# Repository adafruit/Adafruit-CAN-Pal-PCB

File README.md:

## Adafruit CAN Pal - CAN Bus Transciever - TJA1051T/3 PCB

<a href="http://www.adafruit.com/products/5708"><br/>
Click here to purchase one from the Adafruit shop</a>

PCB files for the Adafruit CAN Pal - CAN Bus Transciever - TJA1051T/3. 

Format is EagleCAD schematic and board layout
* https://www.adafruit.com/product/5708

### Description

If you'd like to connect a board with native CAN Peripheral support, the Adafruit CAN Pal Transceiver will take the 3V logic level signals and convert them to CAN logic levels with the differential signaling required to communicate. Note that not all chips have a CAN peripheral! Some that we know do have it are the ESP32/ESP32-S2/ESP32-S3 (note that ESP32 calls this interface TWAI not CAN) series of chips, SAME51, STM32F405, or Teensy 4.

Check the product documentation for the board you are wiring this to, to make sure that the chip has CAN support and the RX and TX pins are brought out for you to connect the transceiver to! Despite sharing the 'RX' and 'TX' name with UART, they're not at all the same interface.

CAN Bus is a small-scale networking standard, originally designed for cars and, yes, busses, but is now used for many robotics or sensor networks that need better range and addressing than I2C, and don't have the pins or computational ability to talk on Ethernet. CAN is 2 wire differential, which means it's good for long distances and noisy environments.

Messages are sent at about 1Mbps rate - you set the frequency for the bus and then all 'joiners' must match it, and have an address before the packet so that each node can listen in to messages just for it. New nodes can be attached easily because they just need to connect to the two data lines anywhere in the shared net. Each CAN devices sends messages whenever it wants, and thanks to some clever data encoding, can detect if there's a message collision and retransmit later. 

We've added a few nice extras to this breakout pal to make it useful in many common CAN scenarios:

* TJA1051/T3 can communicate with 3.3V~5V logic for use with modern microcontrollers. 
* 5V charge-pump voltage generator, so even though you are running 3.3V power and logic on most modern microcontroller boards, it will generate a nice clean 5V as required by the transceiver. No separate 5V power required!
* 3.5mm terminal block that can be soldered in to get quick access to the High and Low data lines as well as a ground pin.
* 2 x 60 ohm termination resistor on board (120 ohm in series), you can remove or activate the termination easily by flipping the onboard switch.

Each order comes with an assembled 'pal, terminal block and header. You will need to solder in the header yourself but its a quick task.

### License

Adafruit invests time and resources providing this open source design, please support Adafruit and open-source hardware by purchasing products from [Adafruit](https://www.adafruit.com)!

Designed by Limor Fried/Ladyada for Adafruit Industries.

Creative Commons Attribution/Share-Alike, all text above must be included in any redistribution. 
See license.txt for additional details.

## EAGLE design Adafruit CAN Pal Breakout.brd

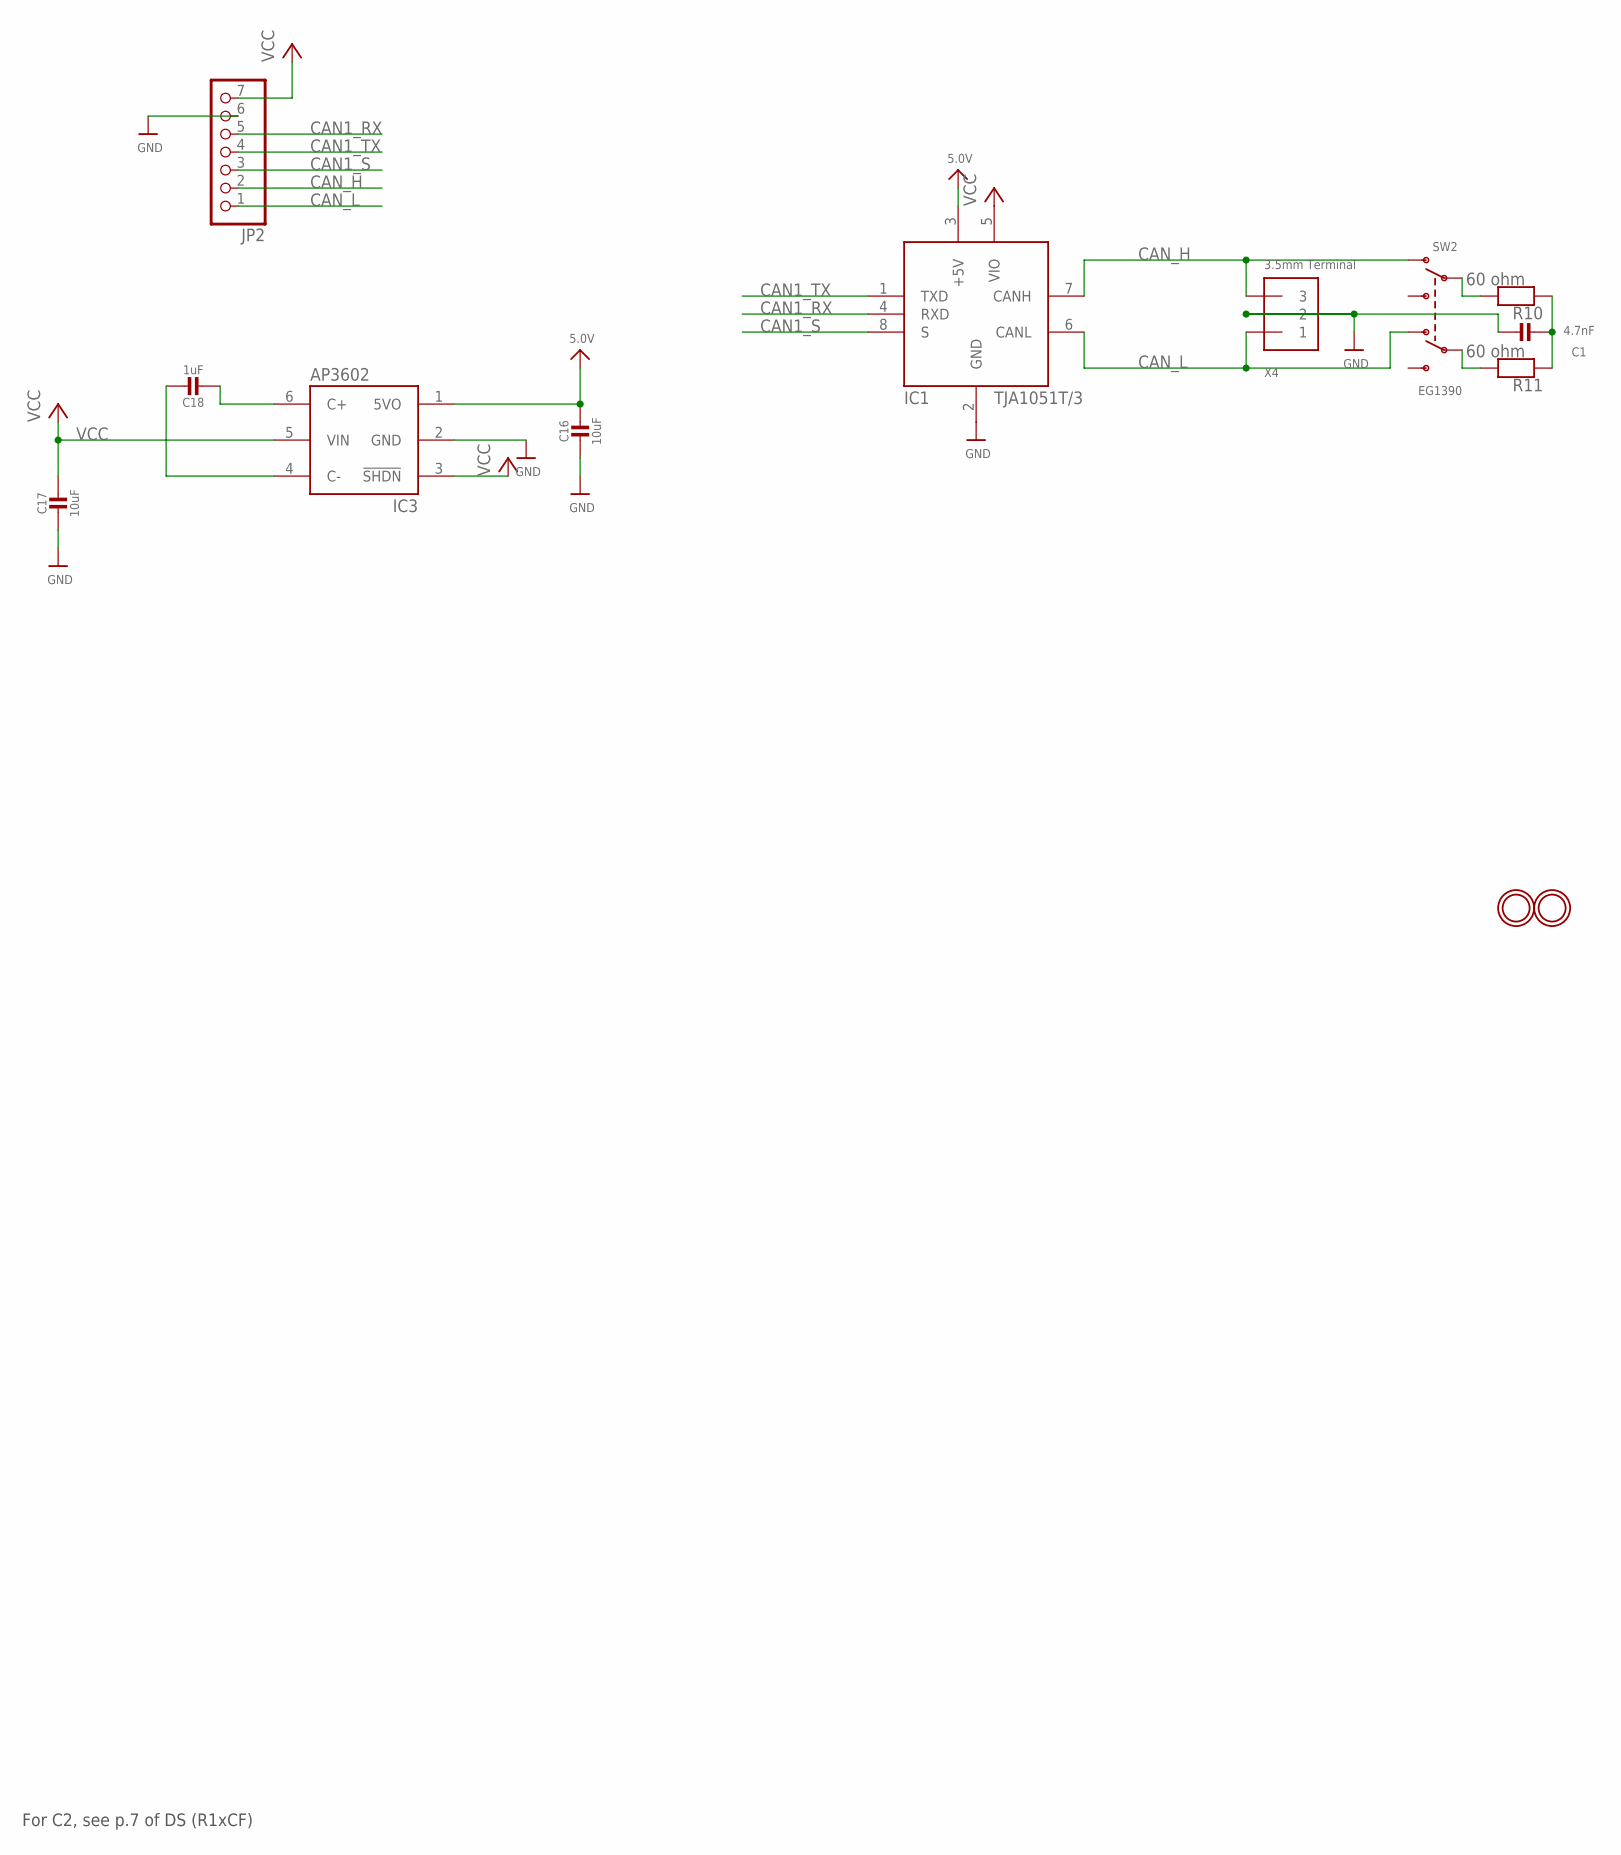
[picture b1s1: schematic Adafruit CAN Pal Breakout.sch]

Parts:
C1: 4.7nF; 0603-NO
C16, C17: 10uF; 0805-NO
C18: 1uF; 0805_10MGAP
IC1: TJA1051T/3; SOIC8_150MIL
IC3: AP3602; SOT23-6
JP2: HEADER-1X770MIL; 1X07_ROUND_70
R10, R11: 60 ohm; 0603-NO
SW2: EG1390
U$2, U$3: MOUNTINGHOLE2.5; MOUNTINGHOLE_2.5_PLATED
X4: 3.5mm Terminal; TERMBLOCK_1X3-3.5MM

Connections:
5.0V: C16.1, IC1.3 (+5V), IC3.1 (5VO)
CAN1_RX: IC1.4 (RXD), JP2.5
CAN1_S: IC1.8 (S), JP2.3
CAN1_TX: IC1.1 (TXD), JP2.4
CAN_H: IC1.7 (CANH), JP2.2, SW2.O1, X4.3
CAN_L: IC1.6 (CANL), JP2.1, SW2.O2, X4.1
GND: C1.2, C16.2, C17.2, IC1.2 (GND), IC3.2 (GND), JP2.6, X4.2
unnamed: R10.2, SW2.P1
unnamed: R11.2, SW2.P2
unnamed: C18.2, IC3.6 (C+)
unnamed: C18.1, IC3.4 (C-)
unnamed: C1.1, R10.1, R11.1
VCC: C17.1, IC1.5 (VIO), IC3.3 (!SHDN), IC3.5 (VIN), JP2.7

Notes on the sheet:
For C2, see p.7 of DS (R1xCF)

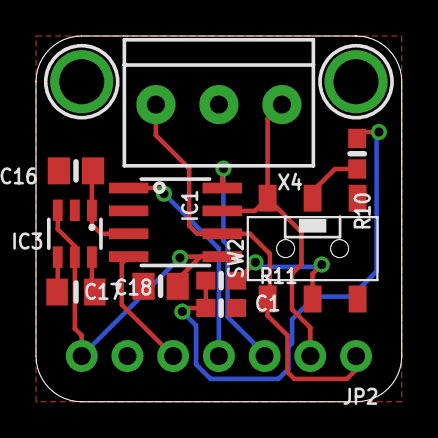
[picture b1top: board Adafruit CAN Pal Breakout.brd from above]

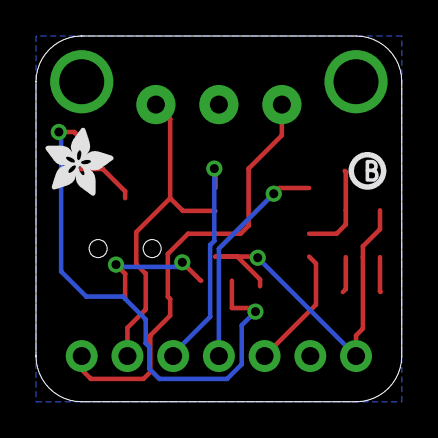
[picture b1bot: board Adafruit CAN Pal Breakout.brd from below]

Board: 2 copper layers, 20.3 x 20.3 mm, 30 parts (5 on the bottom side), 13 nets.

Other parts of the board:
PLABEL0: PLABEL0
PLABEL1: PLABEL1
PLABEL2: PLABEL2
PLABEL3: PLABEL3
PLABEL4: PLABEL4
PLABEL5: PLABEL5
PLABEL6: PLABEL6
PLABEL7: PLABEL7
PLABEL8: PLABEL8
PLABEL9: PLABEL9
PLABEL10: PLABEL10
PLABEL11: PLABEL11
PLABEL12: PLABEL12
PLABEL13: PLABEL13
PLABEL14: PLABEL14
U$6: ADAFRUIT_3.5MM
U$7: PCBFEAT-REV-040

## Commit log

2023-03-22 adding cookiecutter output

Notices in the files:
parts and their libraries:
microbuilder: This work is placed in the public domain, and may be freely used for commercial and non-commercial work with the following conditions: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
